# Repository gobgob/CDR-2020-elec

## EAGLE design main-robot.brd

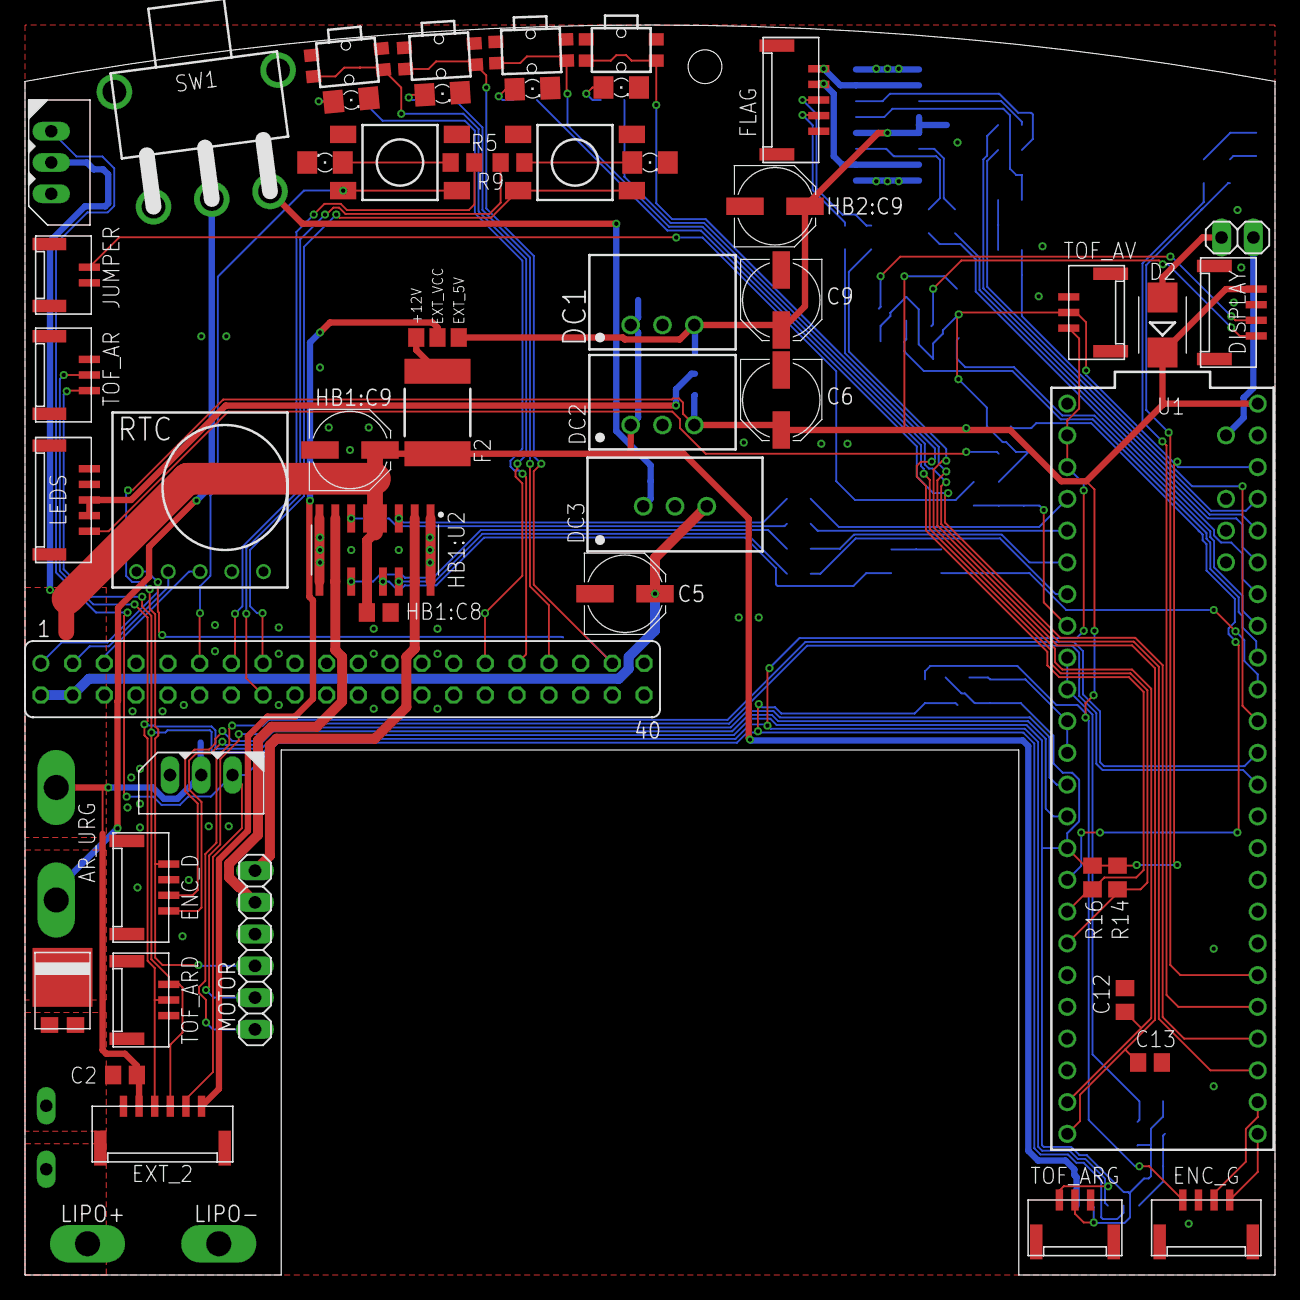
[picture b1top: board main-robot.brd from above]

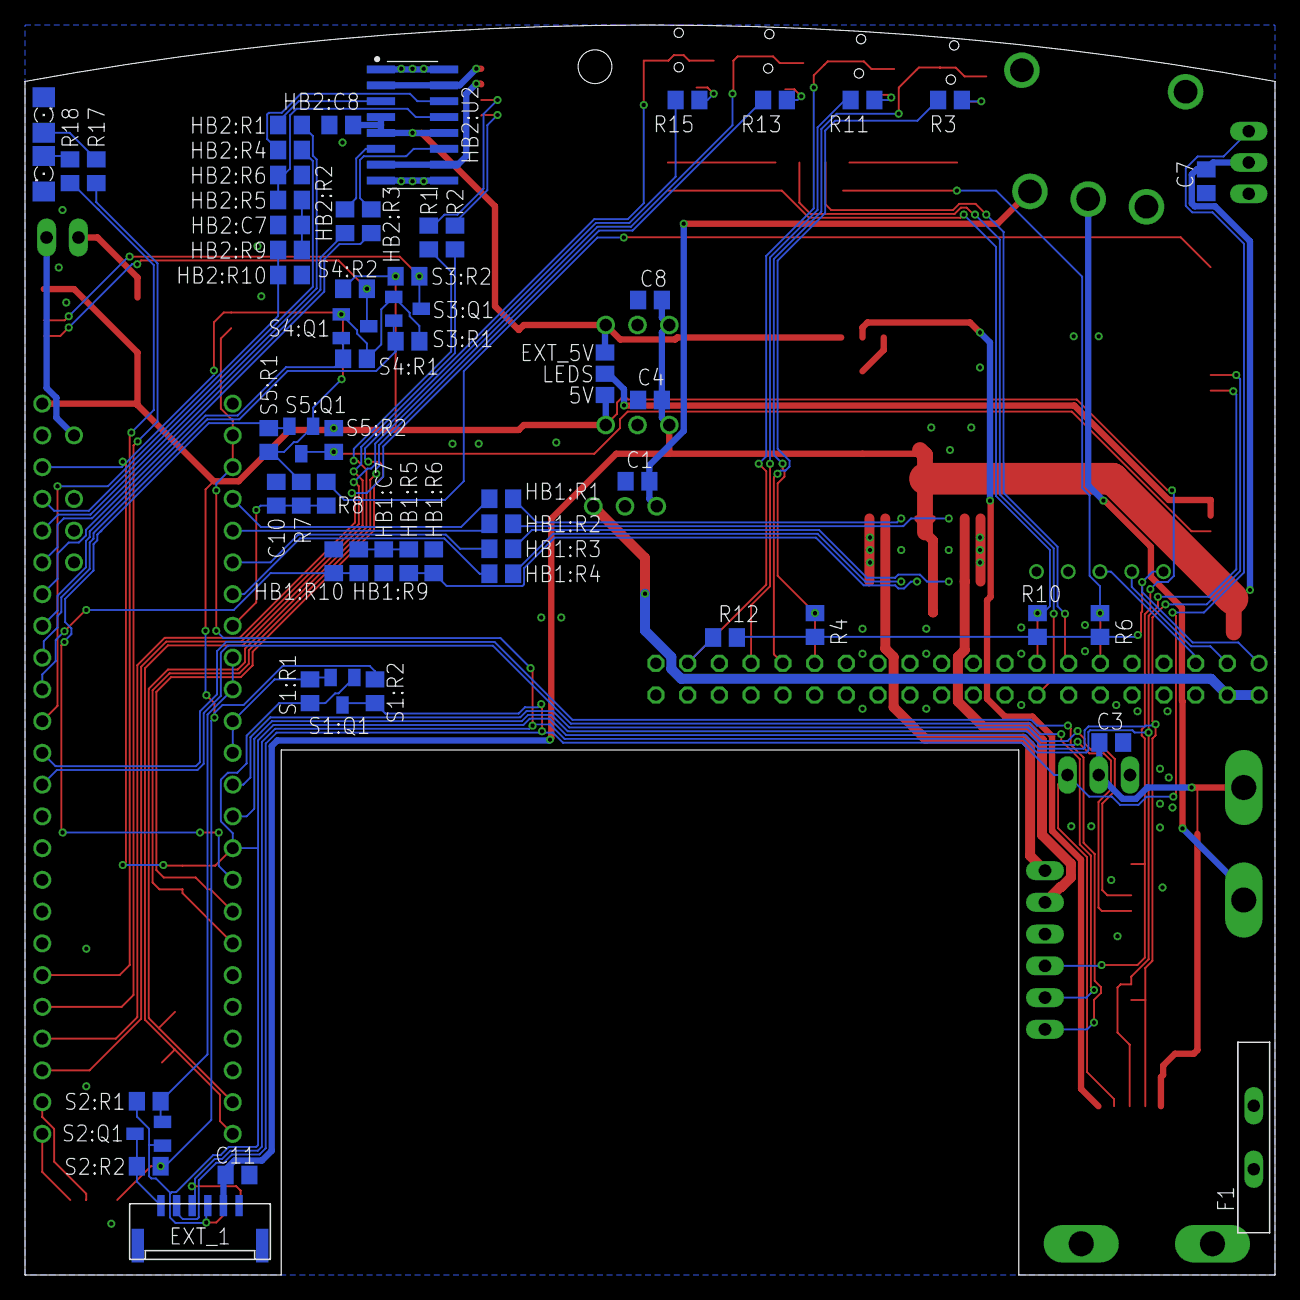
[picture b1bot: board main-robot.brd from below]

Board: 2 copper layers, 100.0 x 100.0 mm, 117 parts (61 on the bottom side), 89 nets.

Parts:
AR-URG-1, AR-URG-2: TPPAD1-20Y; P1-20Y
C1, C4, C8: 22µF; C0805
C2, C3, C7, C11: 10µF; C0805
C5, C6, C9: 220µF; PANASONIC_D
C10, C12, C13: 100nF; C0805
CON1, CON2: AX12; 5267-03A
D1: DIODE_S15P45; TO-277A
D2: SS56B; SMB
DC1, DC2: TSR 1-2450; TSR1
DC3: TSR 2-2450; TSR2
DISPLAY: JST-04TOP; BM04B-GHS
ENC_D: JST-04TOP; BM04B-GHS
ENC_G: JST-04TOP; BM04B-GHS
EXT_1: JST-06SIDE; SM06B-GHS
EXT_2: JST-06TOP; BM06B-GHS
F1: RGEF800; 5MM
F2: MF-LSMF300
FLAG: JST-05TOP; BM05B-GHS
HB1:C7, HB2:C7: 10nF; C0805
HB1:C8, HB2:C8: 100nF; C0805
HB1:C9, HB2:C9: 220µF; PANASONIC_D
HB1:R1, HB1:R2, HB1:R3, HB1:R4, HB1:R6, HB2:R1, HB2:R2, HB2:R3, HB2:R4, HB2:R6: 1k; R0805
HB1:R5, HB1:R9, HB2:R5, HB2:R9: 10k; R0805
HB1:R10, HB2:R10: 15k; R0805
HB1:U2, HB2:U2: VNH7100AS; SOIC127P600X175-16M
JMP1, JMP2: 0R-JUMPA; A0R-JMP
JP1: VUSB; 1X02
JUMPER: JST-02SIDE; SM02B-GHS
LED1, LED2, LED3, LED4, LED5, LED6, LED7, LED8: 1206
LEDS: JST-05SIDE; SM05B-GHS
LIPO+: TPPAD1-20Y; P1-20Y
LIPO-: TPPAD1-20Y; P1-20Y
MOTOR: 1X06
R1, R2, R4, R6, R7, R10, R12, R14, R16: 10k; R0805
R3, R5, R9, R11, R13, R15, R17, R18: 470; R0805
R8: 1k; R0805
RTC1: RTC
S1:Q1, S2:Q1, S3:Q1, S4:Q1, S5:Q1: BSS138; SOT23
S1:R1, S1:R2, S2:R1, S2:R2, S3:R1, S3:R2, S4:R1, S4:R2, S5:R1, S5:R2: 10k; R0805
SV1: RPI; FE20-2
SW1: SWITCH-SPDT-H; SWITCH_SPDT_H
SW2, SW5, SW6, SW7: PUSH-BUTTON436331045822; 436331045822
SW3, SW4: PUSH-BUTTON
TOF_AR: JST-03SIDE; SM03B-GHS
TOF_ARD: JST-03TOP; BM03B-GHS
TOF_ARG: JST-03TOP; BM03B-GHS
TOF_AV: JST-03TOP; BM03B-GHS
U1: TEENSY_3.5_DIL+4

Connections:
3V3: EXT_1.4, EXT_2.4, R7.1, R14.2, R16.2, S1:Q1.1, S1:R1.1, S2:Q1.1, S2:R1.1, S3:Q1.1, S3:R1.1, S4:Q1.1, S4:R1.1, S5:Q1.1, S5:R1.1, TOF_AR.2, TOF_ARD.2, TOF_ARG.2, TOF_AV.2, U1.3.3V, U1.3.3V3
+5V/1: C6.+, D2.C, DC2.3, DISPLAY.4, ENC_D.4, ENC_G.4, JMP2.3, MOTOR.4, S1:R2.1, S2:R2.1, S3:R2.1, S4:R2.1, S5:R2.1, U1.VIN
+5V/2: C5.+, DC3.3, SV1.2, SV1.4
+12V: AR-URG-2.TP, C2.1, C3.1, C4.1, C7.1, C8.1, C11.1, CON1.2, CON2.2, DC1.1, DC2.1, EXT_1.5, EXT_2.5, F2.1, HB1:C8.1, HB1:C9.+, HB1:U2.4, HB1:U2.5, HB1:U2.12
AX12_DATA: CON1.1, CON2.1, EXT_1.2, EXT_2.2, S1:Q1.3, S1:R2.2
AX12_DATA_LV: S1:Q1.2, S1:R1.2, U1.9, U1.10
ENC_D_A: ENC_D.2, U1.11
ENC_D_B: ENC_D.1, U1.12
ENC_G_A: ENC_G.2, U1.34/A15
ENC_G_B: ENC_G.1, U1.33/A14
ENC_MOT_A: MOTOR.5, U1.14/A0
ENC_MOT_B: MOTOR.6, U1.15/A1
EXT_+5V: C9.+, DC1.3, HB2:C8.1, HB2:C9.+, HB2:U2.4, HB2:U2.5, HB2:U2.12, JMP1.1, JMP2.1
EXT_DATA: EXT_1.1, S2:Q1.3, S2:R2.2
EXT_DATA_LV: S2:Q1.2, S2:R1.2, U1.7, U1.8
EXT_VCC: EXT_2.1, JMP1.2
FLAG_CS: HB2:R9.1, HB2:R10.2, U1.16/A2
FLAG_GPIO1: C12.1, R1.1, U1.31/A12
FLAG_GPIO2: C13.1, R2.1, U1.32/A13
FLAG_INA: HB2:R1.1, U1.22/A8
FLAG_INB: HB2:R2.1, U1.21/A7
FLAG_PWM: HB2:R3.1, U1.20/A6
FLAG_SEL: HB2:R4.1, U1.23/A9
GND: C1.2, C2.2, C3.2, C4.2, C5.-, C6.-, C7.2, C8.2, C9.-, C10.1, C11.2, C12.2, C13.2, CON1.3, CON2.3, DC1.2, DC2.2, DC3.2, DISPLAY.3, ENC_D.3, ENC_G.3, EXT_1.6, EXT_2.6, FLAG.1, HB1:C7.1, HB1:C8.2, HB1:C9.-, HB1:R6.1, HB1:R10.1, HB1:U2.1, HB1:U2.8, HB1:U2.9, HB1:U2.16, HB2:C7.1, HB2:C8.2, HB2:C9.-, HB2:R6.1, HB2:R10.1, HB2:U2.1, HB2:U2.8, HB2:U2.9, HB2:U2.16, JUMPER.2, LED1.C, LED2.C, LED3.C, LED4.C, LED5.C, LED6.C, LED7.C, LED8.C, LEDS.1, LEDS.2, LIPO-.TP, MOTOR.3, RTC1.GND, SV1.6, SV1.9, SV1.14, SV1.20, SV1.25, SV1.30, SV1.34, SV1.39, SW1.CASE1, SW1.CASE2, SW2.1, SW2.3, SW3.1, SW3.2, SW4.1, SW4.2, SW5.1, SW5.3, SW6.1, SW6.3, SW7.1, SW7.3, TOF_AR.1, TOF_ARD.1, TOF_ARG.1, TOF_AV.1, U1.AGND, U1.GND, U1.GND1
HB1:N$5: HB1:R3.2, HB1:U2.11
HB1:N$6: HB1:R2.2, HB1:U2.6
HB1:N$7: HB1:R1.2, HB1:U2.3
HB1:N$8: HB1:R4.2, HB1:U2.14
HB1:N$9: HB1:R5.2, HB1:R6.2, HB1:U2.13
HB1:N$13: HB1:C7.2, HB1:R5.1, HB1:R9.2
HB2:N$5: HB2:R3.2, HB2:U2.11
HB2:N$6: HB2:R2.2, HB2:U2.6
HB2:N$7: HB2:R1.2, HB2:U2.3
HB2:N$8: HB2:R4.2, HB2:U2.14
HB2:N$9: HB2:R5.2, HB2:R6.2, HB2:U2.13
HB2:N$13: HB2:C7.2, HB2:R5.1, HB2:R9.2
IN_COLOR_A: R16.1, SW7.2, SW7.4, U1.25
IN_COLOR_B: R14.1, SW6.2, SW6.4, U1.26
IN_JUMPER: C10.2, R7.2, R8.2, U1.6
JUMPER: JUMPER.1, R8.1
LED_COLOR_A: R15.2, U1.35/A16
LED_COLOR_B: R13.2, U1.36/A17
LED_DATA: LEDS.5, S5:Q1.3, S5:R2.2
LED_DATA_LV: S5:Q1.2, S5:R1.2, U1.24
LED_DEBUG_A: R17.2, U1.37/A18
LED_DEBUG_B: R18.2, U1.38/A19
MOT_CS: HB1:R9.1, HB1:R10.2, U1.17/A3
MOT_INA: HB1:R1.1, U1.2
MOT_INB: HB1:R2.1, U1.3
MOT_PWM: HB1:R3.1, U1.4
MOT_SEL: HB1:R4.1, U1.5
unnamed: C1.1, DC3.1, SW1.2
unnamed: D1.+1, D1.+2, F1.P$1
unnamed: HB1:U2.2, HB1:U2.15, MOTOR.1
unnamed: HB1:U2.7, HB1:U2.10, MOTOR.2
unnamed: FLAG.5, HB2:U2.2, HB2:U2.15
unnamed: FLAG.4, HB2:U2.7, HB2:U2.10
unnamed: FLAG.3, R1.2
unnamed: FLAG.2, R2.2
unnamed: LED1.A, R3.1
unnamed: LED8.A, R13.1
unnamed: AR-URG-1.TP, D1.-, SW1.C
unnamed: D2.A, JP1.2
unnamed: RTC1.SDA, SV1.3
unnamed: RTC1.SCL, SV1.5
unnamed: F2.2, JMP1.3
unnamed: LED2.A, R5.1
unnamed: LED3.A, R9.1
unnamed: LED4.A, R11.1
unnamed: LED7.A, R15.1
unnamed: LED5.A, R18.1
unnamed: LED6.A, R17.1
unnamed: JMP2.2, LEDS.3, LEDS.4
RPI_3V3: R4.2, R6.2, R10.2, R12.2, RTC1.VIN, SV1.1
RPI_IN_MATCH: R12.1, SV1.37, SW5.2, SW5.4
RPI_IN_NET1: R6.1, SV1.11, SW3.3, SW3.4
RPI_IN_NET2: R10.1, SV1.15, SW4.3, SW4.4
RPI_IN_PWDN: R4.1, SV1.29, SW2.2, SW2.4
RPI_LED_MATCH: R11.2, SV1.33
RPI_LED_NET1: R5.2, SV1.13
RPI_LED_NET2: R9.2, SV1.16
RPI_LED_PWR: R3.2, SV1.31
SCL: DISPLAY.1, S4:Q1.3, S4:R2.2
SCL_LV: S4:Q1.2, S4:R1.2, U1.19/A5
SDA: DISPLAY.2, S3:Q1.3, S3:R2.2
SDA_LV: S3:Q1.2, S3:R1.2, U1.18/A4
TOF_DATA: EXT_1.3, EXT_2.3, TOF_AR.3, TOF_ARD.3, TOF_ARG.3, TOF_AV.3, U1.0, U1.1
VUSB: JP1.1, U1.VUSB
V_LIPO: F1.P$2, LIPO+.TP

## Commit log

2020-01-07 add main libs and empty .sch
2020-01-08 Add PCB outline
2020-01-13 brd: rpi placement
2020-01-17 add libs
2020-01-19 progess in schematic
2020-01-25 progress on schematic
2020-01-26 v1 schematics
2020-01-26 brd: components placement
2020-01-26 brd: begin routing
2020-01-27 routing in progress
2020-01-28 routing v1
2020-01-29 update libs
2020-01-29 brd: add more GND vias
2020-01-29 brd: add silkscreen
2020-01-31 add connector for rpi with 3D model
2020-01-31 add mini PCB for ext interface
2020-02-03 change Flag connector
2020-02-03 add gerber files
2020-02-03 fix silkscreen
